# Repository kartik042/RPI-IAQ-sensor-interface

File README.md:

An interface board that connects an Indoor Air quality sensor to GPIO pins of a Raspberry Pi that is used to record the data output from the sensor for data analysis.

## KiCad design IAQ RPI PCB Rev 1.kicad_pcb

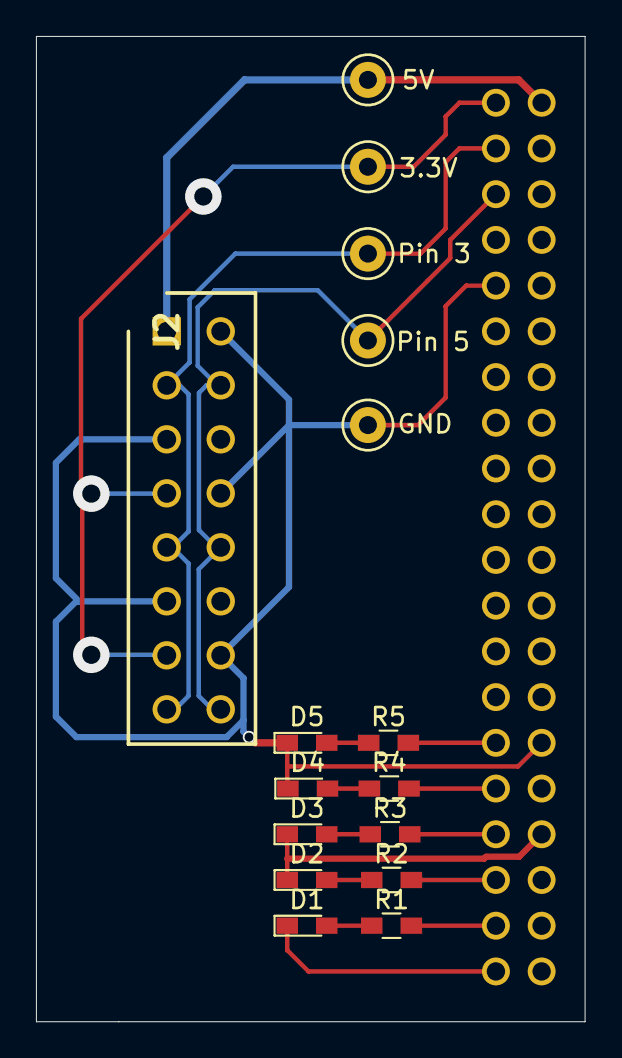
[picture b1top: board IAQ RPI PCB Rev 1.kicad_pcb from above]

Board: 2 copper layers, 30.5 x 54.7 mm, 17 parts (1 on the bottom side), 15 nets.

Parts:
3.3V: 3.3V; Test_Point_Keystone_5000-5004_Miniature
5V: 5V; Test_Point_Keystone_5000-5004_Miniature
D1, D2, D3, D4, D5: LED_ALT; LED_0603_HandSoldering
GND: GND; Test_Point_Keystone_5000-5004_Miniature
J1: Conn_02x20_Odd_Even; SSQ-120-XX-YYY-D
J2: Conn_02x08_Odd_Even; RHDR16W84P300_2X8_2486X686X944P
Pin 3: Pin 3; Test_Point_Keystone_5000-5004_Miniature
Pin 5: Pin 5; Test_Point_Keystone_5000-5004_Miniature
R1, R2, R3, R4, R5: 330; R_0603_HandSoldering

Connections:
GND: D1.1, D2.1, D3.1, D4.1, D5.1, GND.1, J1.9, J1.30, J1.34, J1.39, J2.2, J2.5, J2.8, J2.11, J2.14
unnamed: D1.2, R1.1
unnamed: D2.2, R2.1
unnamed: D3.2, R3.1
unnamed: D4.2, R4.1
unnamed: D5.2, R5.1
unnamed: 3.3V.1, J1.1, J2.7, J2.13
unnamed: J1.3, J2.3, J2.9, J2.15, Pin 3.1
unnamed: J1.5, J2.4, J2.10, J2.16, Pin 5.1
unnamed: J1.29, R5.2
unnamed: J1.31, R4.2
unnamed: J1.33, R3.2
unnamed: J1.35, R2.2
unnamed: J1.37, R1.2
VCC: 5V.1, J1.2, J2.1
